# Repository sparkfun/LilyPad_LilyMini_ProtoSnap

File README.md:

LilyMini ProtoSnap
========================================

[*LilyMini ProtoSnap (https://www.sparkfun.com/products/14063)*](https://www.sparkfun.com/products/14063)

The LilyMini ProtoSnap is a great way to create interactive e-textile circuits. At the center of the board is a pre-programmed LilyMini microcontroller connected to a LilyPad Light Sensor, LilyPad Button and two pairs of LilyPad LEDs.

Like other ProtoSnap boards, the LilyMini ProtoSnap has all of these parts connected together on the board, enabling you to play with the circuit before you sew. When you're ready to make your project, snap out the parts and sew them together!

The LilyMini ProtoSnap ships with pre-loaded code that exercises all the LilyPad pieces connected to it. The sample code has three modes, which can be selected by pressing the LilyPad Button on the bottom-left side of the ProtoSnap. The built-in RGB LED on the LilyMini will change color to indicate which mode has been selected:

* White: All LEDs on.
* Magenta: LEDs fade in and out in a breathing pattern. When the light sensor is covered, LEDs fade faster.
* Cyan/Blue: When the board is in darkness, the LEDs will twinkle (perfect for night-lights)

You can use the built-in code to make your own projects (see the hook-up guide below), or you can reprogram the LilyMini using the Arduino system . **Reprogramming instructions coming soon (1/1/17).** 

Repository Contents
-------------------

This repository includes the hardware design files and binaries for the release firmware. <br>
**Reprogramming information and source code are coming soon (1/1/17).** 

* **/Documentation** - Data sheets, additional product information
* **/Firmware** - Preinstalled code 
* **/Hardware** - Eagle design files (.brd, .sch)
* **/Production** - Production panel files (.brd)

Documentation
--------------
* **[Hookup Guide](https://learn.sparkfun.com/tutorials/lilymini-protosnap-hookup-guide)** - Basic hookup guide and example projects for the LilyMini ProtoSnap

License Information
-------------------

This product is _**open source**_! Please review the LICENSE.md file for license information. If you have any questions or concerns on licensing, please contact techsupport@sparkfun.com. This information is distributed as-is; no warranty is given.

Have fun! - Your friends at SparkFun.

Acknowledgement
---------------

We gratefully acknowledge the following people and groups for their open-source contributions:

* Arduino LLC and Atmel Corporation/Thibaut Viard for bringing Arduino support to the SAMD21.
* Justin Mattair of [Mattairtech, Inc.](https://www.mattairtech.com/) for porting Arduino's SAMD21 bootloader and Shumatech's BOSSAC to the SAMD11.

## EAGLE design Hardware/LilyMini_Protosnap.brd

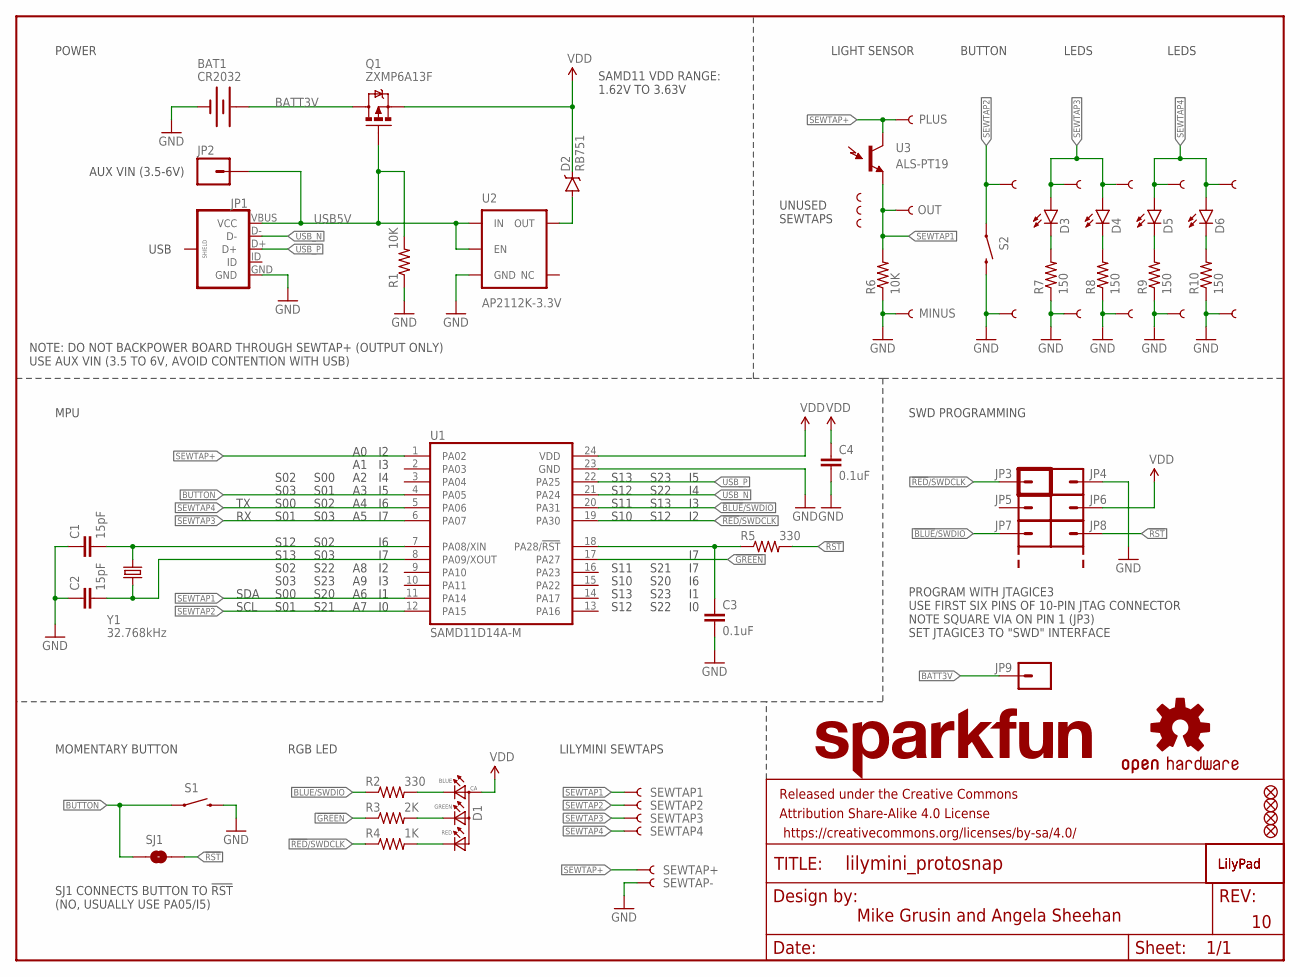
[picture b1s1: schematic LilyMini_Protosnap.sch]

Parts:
$1_61_$_2016-09-25_21-56-09: OSHW-LOGOS; OSHW-LOGO-S
BAT1: CR2032; BATTERY_20MM_PTH_KIT
C1, C2: 15pF; 0603-CAP
C3, C4: 0.1uF; 0603-CAP
D1: 0.13_RGB_LEDPLCC; P-LCC-4-3
D2: RB751; SOD-523
D3, D4, D5, D6: LED-WHITE1206; LED-1206
FD1, FD2, FD3, FD4: FIDUCIAL1X2; FIDUCIAL-1X2
FRAME1: FRAME-LETTER; CREATIVE_COMMONS
JP1: USB_MICROB_PLUGUSB-B-MICRO-SMD-VERT; USB-B-MICRO-SMD_VERT
JP2: M01SMDNS; 1X01NS
JP3: M01_POGOPAD_20M_NS_1S_SQUARE; 1X01_POGOPIN_PAD_NOSILK_1SIDE_SQUARE
JP4, JP5, JP6, JP7, JP8, JP9: M01_POGOPAD_20M_NS_1S_ROUND; 1X01_POGOPIN_PAD_NOSILK_1SIDE_ROUND
JP12, JP13: SEWTAP8; PETAL-MEDIUM-2SIDE
JP20, JP21, JP22, JP23, JP24, JP25, JP26, JP27: SEWTAP6; PETAL-SMALL-2SIDE
LOGO1: LOGO-LPL; LOGO-L
LOGO2: LILYLOGO-L-TOP; LOGO-L-TOP
LOGO4: SFE_LOGO_NAME.1_INCH; SFE_LOGO_NAME_.1
Q1: ZXMP6A13F; SOT23-3
R1, R6: 10K; 0603-RES
R2, R5: 330; 0603-RES
R3: 2K; 0603-RES
R4: 1K; 0603-RES
R7, R8, R9, R10: 150; 0603-RES
S1: SWITCH-MOMENTARY-2SMD-4.6X2.8MM; TACTILE_SWITCH_SMD_4.6X2.8MM
S2: SWITCH-MOMENTARY-2SMD-REDUNDANT; TACTILE-SWITCH-SMD
SEWTAP1, SEWTAP2, SEWTAP3, SEWTAP4: SEWTAP8; PETAL-MEDIUM-2SIDE
SEWTAP+: SEWTAP8; PETAL-MEDIUM-2SIDE
SEWTAP-: SEWTAP8; PETAL-MEDIUM-2SIDE
SEWTAPLS+: PLUS; PETAL-SMALL-2SIDE
SEWTAPLS-: MINUS; PETAL-SMALL-2SIDE
SEWTAPLSOUT: OUT; PETAL-SMALL-2SIDE
SJ1: JUMPER-PAD-2-NO; PAD-JUMPER-2-NO_NO_SILK
ST1, ST2, ST3: SEWTAP-NOHOLE2; PETAL-NOHOLE-2SIDE
U1: SAMD11D14A-M; QFN-24_ALT2
U2: AP2112K-3.3V; SOT23-5
U3: ALS-PT19
Y1: 32.768kHz; CRYSTAL-SMD-3.2X1.5MM

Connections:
!BLUE!/SWDIO: JP7.P$1, R2.1, U1.20 (PA31)
!GREEN!: R3.1, U1.17 (PA27)
!RED!/SWDCLK: JP3.P$1, R4.1, U1.19 (PA30)
!RST!: JP8.P$1, R5.2, SJ1.2
!RST!1: C3.1, R5.1, U1.18 (PA28/!RST!)
B: D1.3 (BLUE), R2.2
BATT3V: BAT1.+1 (+), BAT1.+2 (+), JP9.P$1, Q1.3 (D)
BUTTON: S1.1, S1.2 (1), SJ1.1, U1.4 (PA05)
G: D1.2 (GREEN), R3.2
GND: BAT1.-3 (-), C1.1, C2.1, C3.2, C4.2, JP1.GND, JP4.P$1, JP13.1, JP21.1, JP23.1, JP25.1, JP27.1, R1.1, R6.1, R7.1, R8.1, R9.1, R10.1, S1.3 (2), S1.4 (2), S2.3 (2), S2.4 (2), SEWTAP-.1, SEWTAPLS-.1, U1.23 (GND), U2.2 (GND)
unnamed: D2.A, U2.5 (OUT)
unnamed: D3.C, R7.2
unnamed: D4.C, R8.2
unnamed: D5.C, R9.2
unnamed: D6.C, R10.2
R: D1.1 (RED), R4.2
SEWTAP1: R6.2, SEWTAP1.1, SEWTAPLSOUT.1, U1.11 (PA14), U3.E (E1)
SEWTAP2: JP12.1, S2.1, S2.2 (1), SEWTAP2.1, U1.12 (PA15)
SEWTAP3: D3.A, D4.A, JP20.1, JP22.1, SEWTAP3.1, U1.6 (PA07)
SEWTAP4: D5.A, D6.A, JP24.1, JP26.1, SEWTAP4.1, U1.5 (PA06)
SEWTAP+: SEWTAP+.1, SEWTAPLS+.1, U1.1 (PA02), U3.C (C1)
USB5V: JP1.VBUS (VCC), JP2.1, Q1.1 (G), R1.2, U2.1 (IN), U2.3 (EN)
USB_N: JP1.D-, U1.21 (PA24)
USB_P: JP1.D+, U1.22 (PA25)
VDD: C4.1, D1.4 (ANODE), D2.C, JP6.P$1, Q1.2 (S), U1.24 (VDD)
X1: C1.2, U1.7 (PA08/XIN), Y1.P$2 (2)
X2: C2.2, U1.8 (PA09/XOUT), Y1.P$1 (1)

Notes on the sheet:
PROGRAM WITH JTAGICE3 USE FIRST SIX PINS OF 10-PIN JTAG CONNECTOR NOTE SQUARE VIA ON PIN 1 (JP3) SET JTAGICE3 TO "SWD" INTERFACE
SAMD11 VDD RANGE: 1.62V TO 3.63V
SWD PROGRAMMING
RGB LED
MOMENTARY BUTTON
S00
S01
S03
S02
SDA
SCL
AUX VIN (3.5-6V)
UNUSED SEWTAPS
Mike Grusin and Angela Sheehan
LILYMINI SEWTAPS
S22
S23
S20
S21
LIGHT SENSOR
BUTTON
LEDS
USB
NOTE: DO NOT BACKPOWER BOARD THROUGH SEWTAP+ (OUTPUT ONLY) USE AUX VIN (3.5 TO 6V, AVOID CONTENTION WITH USB)
S12
S13
S11
S10
POWER
MPU
SJ1 CONNECTS BUTTON TO !RST! (NO, USUALLY USE PA05/I5)

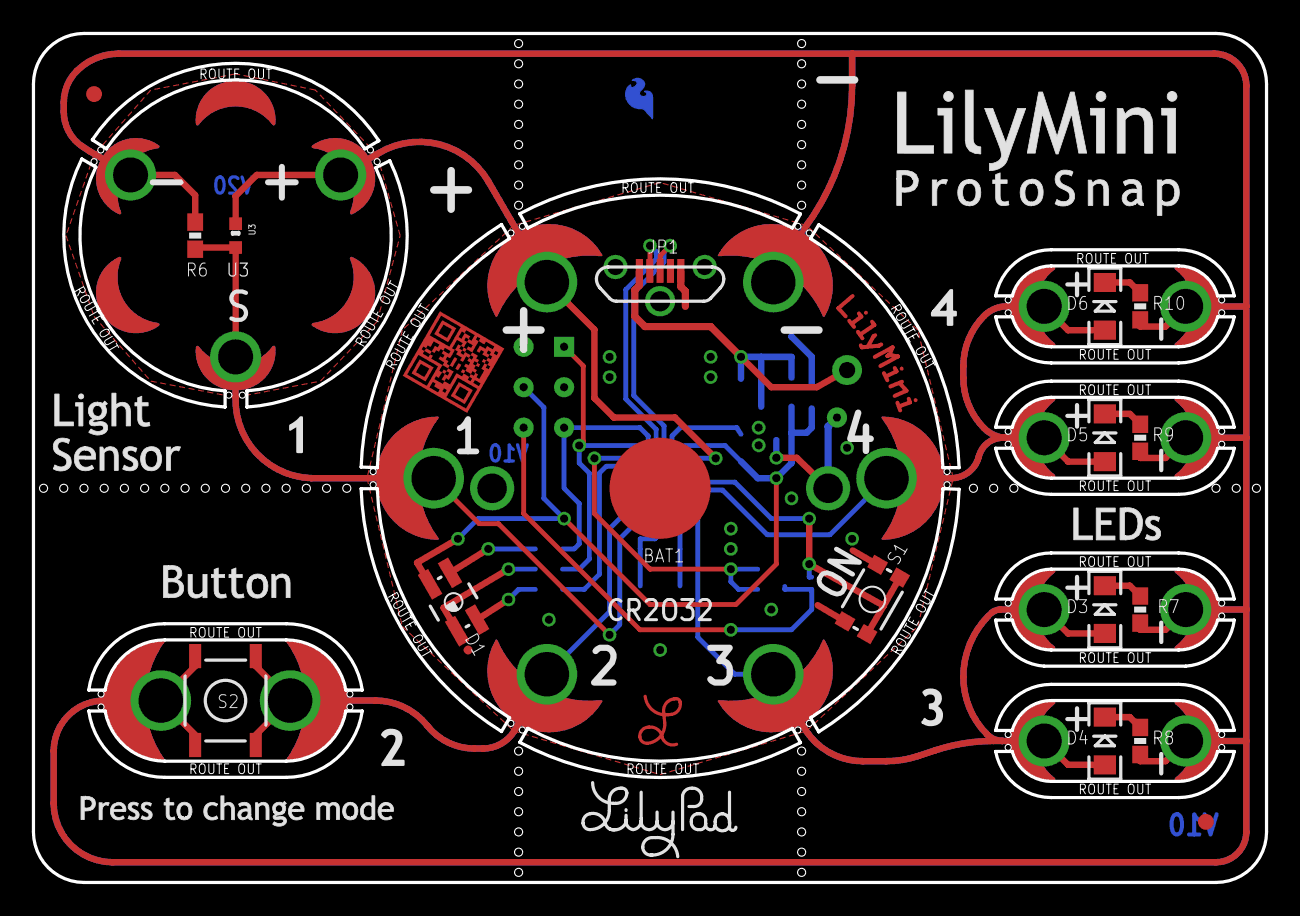
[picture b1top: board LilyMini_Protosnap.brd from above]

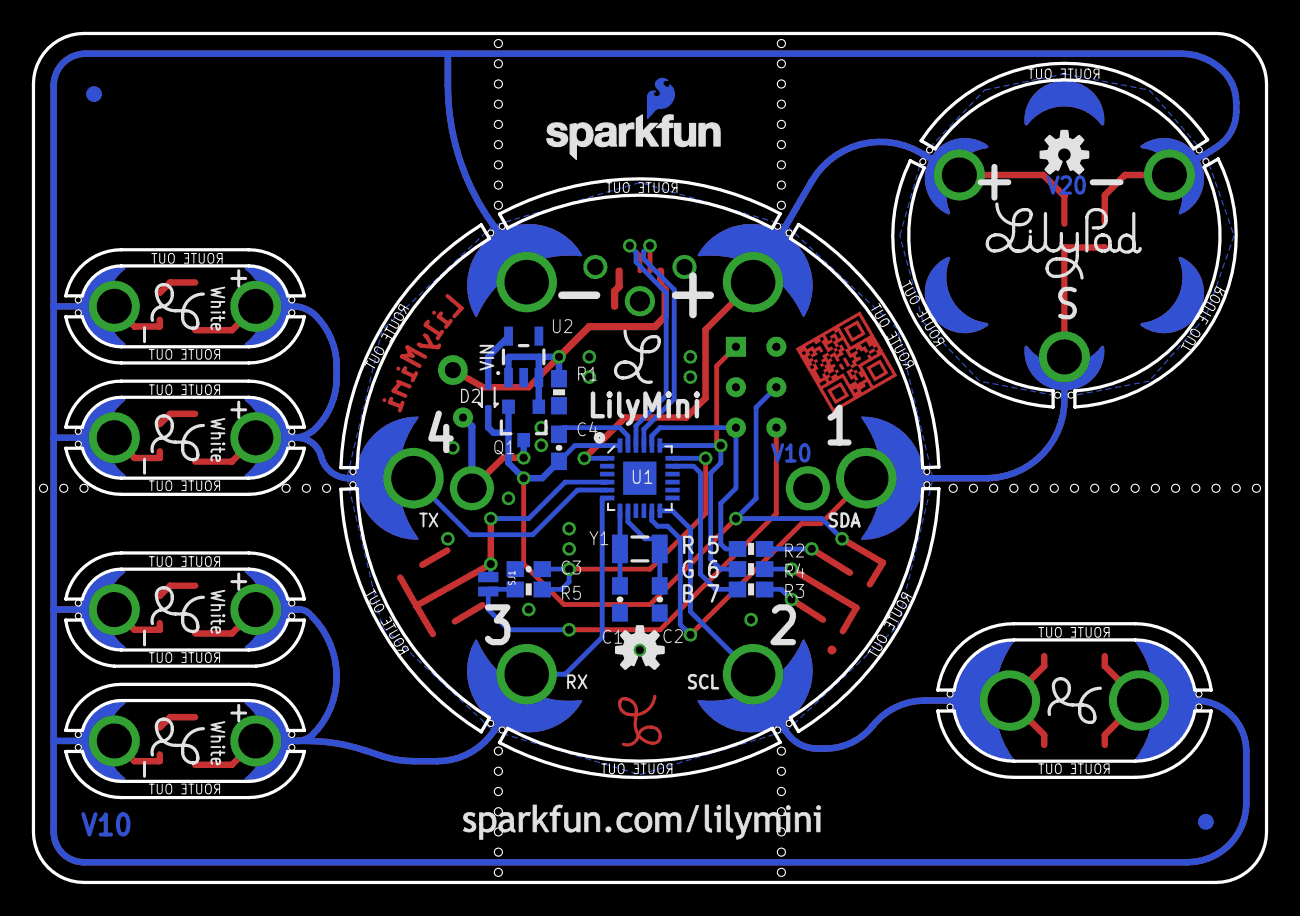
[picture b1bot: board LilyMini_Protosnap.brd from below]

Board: 2 copper layers, 77.5 x 53.3 mm, 78 parts (35 on the bottom side), 27 nets.

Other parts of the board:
LOGO3: OSHW-LOGOS; OSHW-LOGO-S
U$1: LOGO-LILYPAD
U$2: LOGO-LPLP; LOGO-LILYPAD
U$4: SFE_LOGO_FLAME_COPPER_EXPOSED_.1
U$5, U$6, U$7, U$8, U$9: LOGO-L

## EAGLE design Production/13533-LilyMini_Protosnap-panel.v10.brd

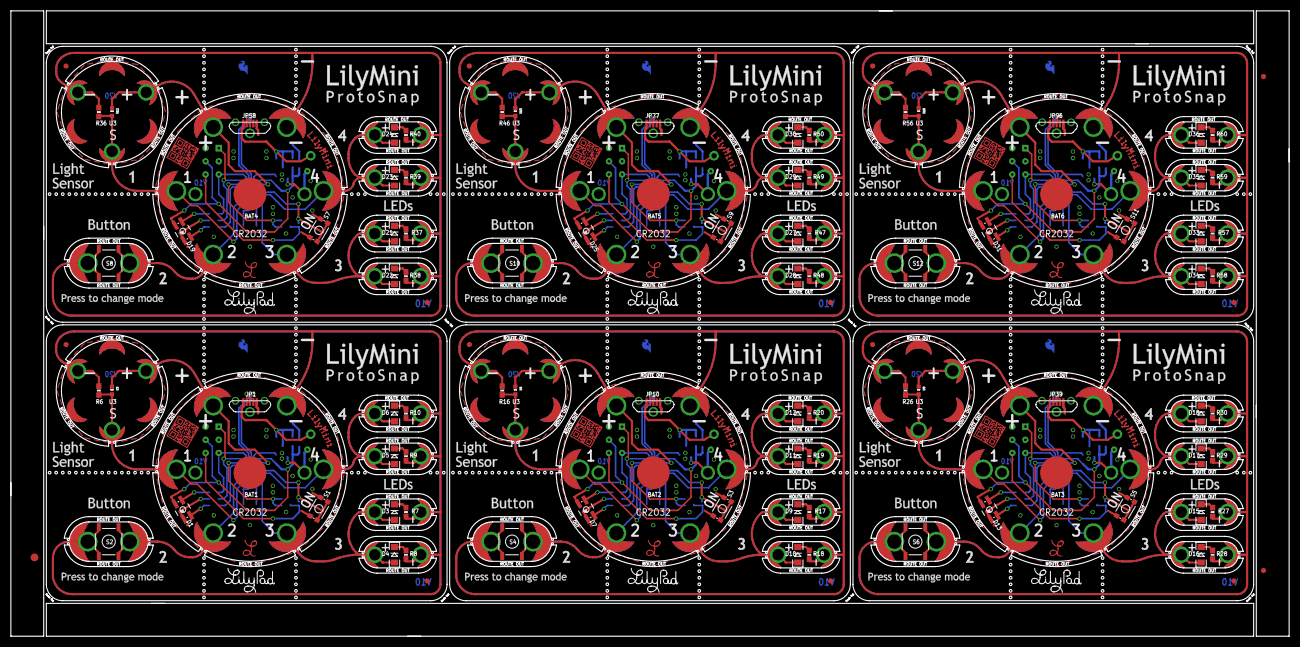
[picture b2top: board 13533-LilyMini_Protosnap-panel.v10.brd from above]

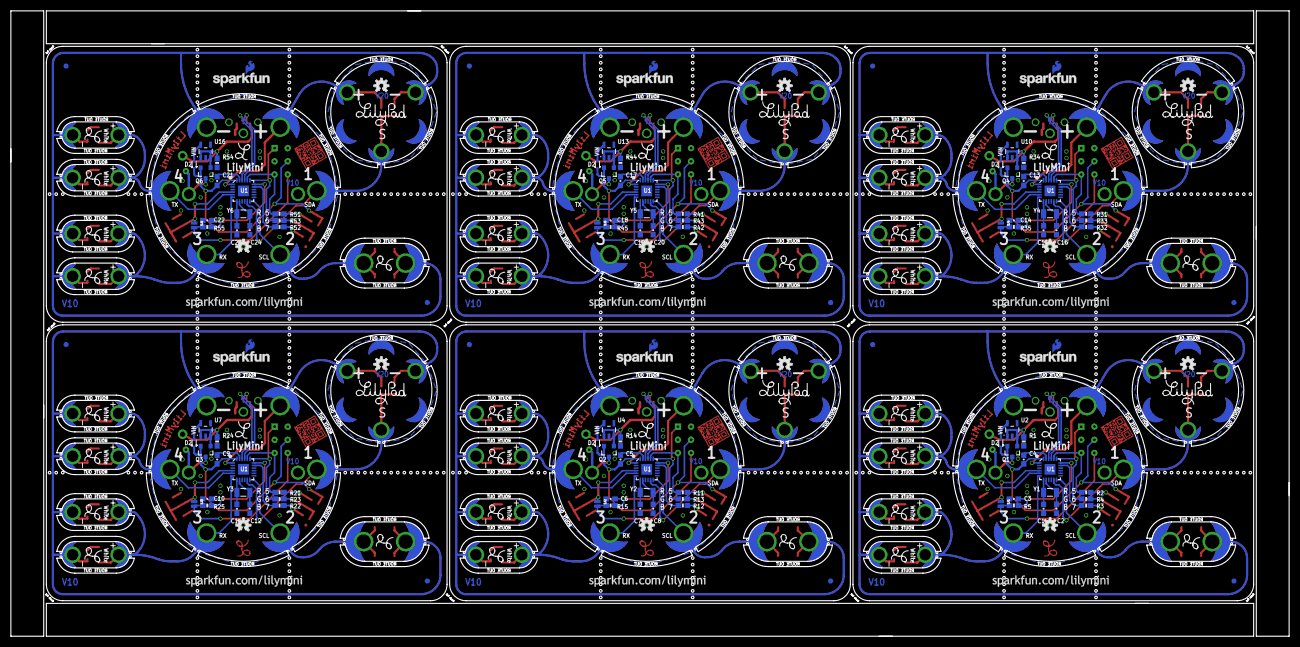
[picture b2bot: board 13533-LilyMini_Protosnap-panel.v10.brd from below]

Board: 2 copper layers, 247.1 x 120.9 mm, 465 parts (210 on the bottom side), 162 nets.

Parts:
$1_61_$_2016-09-25_21-56-01, $1_61_$_2016-09-25_21-56-02, $1_61_$_2016-09-25_21-56-03, $1_61_$_2016-09-25_21-56-04, $1_61_$_2016-09-25_21-56-05, $1_61_$_2016-09-25_21-56-09: OSHW-LOGOS; OSHW-LOGO-S
BAT1, BAT2, BAT3, BAT4, BAT5, BAT6: CR2032; BATTERY_20MM_PTH_KIT
C1, C2, C7, C8, C11, C12, C15, C16, C19, C20, C23, C24: 15pF; 0603-CAP
C3, C4, C5, C6, C9, C10, C13, C14, C17, C18, C21, C22: 0.1uF; 0603-CAP
D1, D7, D13, D19, D25, D31: P-LCC-4-3
D2, D8, D14, D20, D26, D32: RB751; SOD-523
D3, D4, D5, D6, D9, D10, D11, D12, D15, D16, D17, D18, D21, D22, D23, D24, D27, D28, D29, D30, D33, D34, D35, D36: LED-1206
E$1: FIDUCIAL-1.5X3
E$7, E$8: FIDUCIAL-1X2
FD1, FD2, FD3, FD4, FD5, FD6, FD7, FD8, FD9, FD10, FD11, FD12, FD13, FD14, FD15, FD16, FD17, FD18, FD19, FD20, FD21, FD22, FD23, FD24: FIDUCIAL1X2; FIDUCIAL-1X2
JP1, JP10, JP39, JP58, JP77, JP96: USB-B-MICRO-SMD_VERT
JP2, JP19, JP46, JP65, JP84, JP103: 1X01NS
JP3, JP11, JP40, JP59, JP78, JP97: 1X01_POGOPIN_PAD_NOSILK_1SIDE_SQUARE
JP4, JP5, JP6, JP7, JP8, JP9, JP14, JP15, JP16, JP17, JP18, JP38, JP41, JP42, JP43, JP44, JP45, JP57, JP60, JP61, JP62, JP63, JP64, JP76, JP79, JP80, JP81, JP82, JP83, JP95, JP98, JP99, JP100, JP101, JP102, JP114: 1X01_POGOPIN_PAD_NOSILK_1SIDE_ROUND
JP12, JP13, JP32, JP33, JP51, JP52, JP70, JP71, JP89, JP90, JP108, JP109: PETAL-MEDIUM-2SIDE
JP20, JP21, JP22, JP23, JP24, JP25, JP26, JP27, JP28, JP29, JP30, JP31, JP34, JP35, JP36, JP37, JP47, JP48, JP49, JP50, JP53, JP54, JP55, JP56, JP66, JP67, JP68, JP69, JP72, JP73, JP74, JP75, JP85, JP86, JP87, JP88, JP91, JP92, JP93, JP94, JP104, JP105, JP106, JP107, JP110, JP111, JP112, JP113: PETAL-SMALL-2SIDE
LOGO1, LOGO5, LOGO9, LOGO13, LOGO17, LOGO21: LOGO-L
LOGO2, LOGO6, LOGO10, LOGO14, LOGO18, LOGO22: LOGO-L-TOP
LOGO3, LOGO7, LOGO11, LOGO15, LOGO19, LOGO23: OSHW-LOGOS; OSHW-LOGO-S
LOGO4, LOGO8, LOGO12, LOGO16, LOGO20, LOGO24: SFE_LOGO_NAME.1_INCH; SFE_LOGO_NAME_.1
Q1, Q2, Q3, Q4, Q5, Q6: ZXMP6A13F; SOT23-3
R1, R6, R14, R16, R24, R26, R34, R36, R44, R46, R54, R56: 10K; 0603-RES
R2, R5, R11, R15, R21, R25, R31, R35, R41, R45, R51, R55: 330; 0603-RES
R3, R12, R22, R32, R42, R52: 2K; 0603-RES
R4, R13, R23, R33, R43, R53: 1K; 0603-RES
R7, R8, R9, R10, R17, R18, R19, R20, R27, R28, R29, R30, R37, R38, R39, R40, R47, R48, R49, R50, R57, R58, R59, R60: 150; 0603-RES
S1, S3, S5, S7, S9, S11: TACTILE_SWITCH_SMD_4.6X2.8MM
S2, S4, S6, S8, S10, S12: TACTILE-SWITCH-SMD
SEWTAP1, SEWTAP2, SEWTAP3, SEWTAP4, SEWTAP5, SEWTAP6, SEWTAP7, SEWTAP8, SEWTAP9, SEWTAP10, SEWTAP11, SEWTAP12, SEWTAP13, SEWTAP14, SEWTAP15, SEWTAP16, SEWTAP17, SEWTAP18, SEWTAP19, SEWTAP20, SEWTAP21, SEWTAP22, SEWTAP23, SEWTAP24: PETAL-MEDIUM-2SIDE
SEWTAP+, SEWTAP+1, SEWTAP+2, SEWTAP+3, SEWTAP+4, SEWTAP+5: PETAL-MEDIUM-2SIDE
SEWTAP-, SEWTAP-1, SEWTAP-2, SEWTAP-3, SEWTAP-4, SEWTAP-5: PETAL-MEDIUM-2SIDE
SEWTAPLS+, SEWTAPLS+1, SEWTAPLS+2, SEWTAPLS+3, SEWTAPLS+4, SEWTAPLS+5: PLUS; PETAL-SMALL-2SIDE
SEWTAPLS-, SEWTAPLS-1, SEWTAPLS-2, SEWTAPLS-3, SEWTAPLS-4, SEWTAPLS-5: MINUS; PETAL-SMALL-2SIDE
SEWTAPLSOUT, SEWTAPLSOUT1, SEWTAPLSOUT2, SEWTAPLSOUT3, SEWTAPLSOUT4, SEWTAPLSOUT5: OUT; PETAL-SMALL-2SIDE
SJ1, SJ2, SJ3, SJ4, SJ5, SJ6: PAD-JUMPER-2-NO_NO_SILK
ST1, ST2, ST3, ST4, ST5, ST6, ST7, ST8, ST9, ST10, ST11, ST12, ST13, ST14, ST15, ST16, ST17, ST18: PETAL-NOHOLE-2SIDE
U1, U5, U8, U11, U14, U17: SAMD11D14A-M; QFN-24_ALT2
U2, U4, U7, U10, U13, U16: AP2112K-3.3V; SOT23-5
U3, U6, U9, U12, U15, U18: ALS-PT19
U$1, U$13, U$21, U$29, U$37, U$45: LOGO-LILYPAD
U$2, U$3, U$17, U$25, U$33, U$41: LOGO-LPLP; LOGO-LILYPAD
U$4, U$10, U$18, U$26, U$34, U$42: SFE_LOGO_FLAME_COPPER_EXPOSED_.1
U$5, U$6, U$7, U$8, U$9, U$11, U$12, U$14, U$15, U$16, U$19, U$20, U$22, U$23, U$24, U$27, U$28, U$30, U$31, U$32, U$35, U$36, U$38, U$39, U$40, U$43, U$44, U$46, U$47, U$48: LOGO-L
Y1, Y2, Y3, Y4, Y5, Y6: 32.768kHz; CRYSTAL-SMD-3.2X1.5MM

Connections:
!BLUE!/SWDIO: JP7.P$1, R2.1, U1.20
!BLUE!/SWDIO1: JP17.P$1, R11.1, U5.20
!BLUE!/SWDIO2: JP44.P$1, R21.1, U8.20
!BLUE!/SWDIO3: JP63.P$1, R31.1, U11.20
!BLUE!/SWDIO4: JP82.P$1, R41.1, U14.20
!BLUE!/SWDIO5: JP101.P$1, R51.1, U17.20
!GREEN!: R3.1, U1.17
!GREEN!1: R12.1, U5.17
!GREEN!2: R22.1, U8.17
!GREEN!3: R32.1, U11.17
!GREEN!4: R42.1, U14.17
!GREEN!5: R52.1, U17.17
!RED!/SWDCLK: JP3.P$1, R4.1, U1.19
!RED!/SWDCLK1: JP11.P$1, R13.1, U5.19
!RED!/SWDCLK2: JP40.P$1, R23.1, U8.19
!RED!/SWDCLK3: JP59.P$1, R33.1, U11.19
!RED!/SWDCLK4: JP78.P$1, R43.1, U14.19
!RED!/SWDCLK5: JP97.P$1, R53.1, U17.19
!RST!: JP8.P$1, R5.2, SJ1.2
!RST!1: C3.1, R5.1, U1.18
!RST!2: JP18.P$1, R15.2, SJ2.2
!RST!3: C6.1, R15.1, U5.18
!RST!4: JP45.P$1, R25.2, SJ3.2
!RST!5: C10.1, R25.1, U8.18
!RST!6: JP64.P$1, R35.2, SJ4.2
!RST!7: C14.1, R35.1, U11.18
!RST!8: JP83.P$1, R45.2, SJ5.2
!RST!9: C18.1, R45.1, U14.18
!RST!10: JP102.P$1, R55.2, SJ6.2
!RST!11: C22.1, R55.1, U17.18
B: D1.3, R2.2
B1: D7.3, R11.2
B2: D13.3, R21.2
B3: D19.3, R31.2
B4: D25.3, R41.2
B5: D31.3, R51.2
BATT3V: BAT1.+1, BAT1.+2, JP9.P$1, Q1.3
BATT3V1: BAT2.+1, BAT2.+2, JP38.P$1, Q2.3
BATT3V2: BAT3.+1, BAT3.+2, JP57.P$1, Q3.3
BATT3V3: BAT4.+1, BAT4.+2, JP76.P$1, Q4.3
BATT3V4: BAT5.+1, BAT5.+2, JP95.P$1, Q5.3
BATT3V5: BAT6.+1, BAT6.+2, JP114.P$1, Q6.3
BUTTON: S1.1, S1.2, SJ1.1, U1.4
BUTTON1: S3.1, S3.2, SJ2.1, U5.4
BUTTON2: S5.1, S5.2, SJ3.1, U8.4
BUTTON3: S7.1, S7.2, SJ4.1, U11.4
BUTTON4: S9.1, S9.2, SJ5.1, U14.4
BUTTON5: S11.1, S11.2, SJ6.1, U17.4
G: D1.2, R3.2
G1: D7.2, R12.2
G2: D13.2, R22.2
G3: D19.2, R32.2
G4: D25.2, R42.2
G5: D31.2, R52.2
GND: BAT1.-3, C1.1, C2.1, C3.2, C4.2, JP1.GND, JP4.P$1, JP13.1, JP21.1, JP23.1, JP25.1, JP27.1, R1.1, R6.1, R7.1, R8.1, R9.1, R10.1, S1.3, S1.4, S2.3, S2.4, SEWTAP-.1, SEWTAPLS-.1, U1.23, U2.2
GND1: BAT2.-3, C5.2, C6.2, C7.1, C8.1, JP10.GND, JP14.P$1, JP28.1, JP29.1, JP30.1, JP31.1, JP32.1, R14.1, R16.1, R17.1, R18.1, R19.1, R20.1, S3.3, S3.4, S4.3, S4.4, SEWTAP-1.1, SEWTAPLS-1.1, U4.2, U5.23
GND3: BAT3.-3, C9.2, C10.2, C11.1, C12.1, JP39.GND, JP41.P$1, JP47.1, JP48.1, JP49.1, JP50.1, JP51.1, R24.1, R26.1, R27.1, R28.1, R29.1, R30.1, S5.3, S5.4, S6.3, S6.4, SEWTAP-2.1, SEWTAPLS-2.1, U7.2, U8.23
GND6: BAT4.-3, C13.2, C14.2, C15.1, C16.1, JP58.GND, JP60.P$1, JP66.1, JP67.1, JP68.1, JP69.1, JP70.1, R34.1, R36.1, R37.1, R38.1, R39.1, R40.1, S7.3, S7.4, S8.3, S8.4, SEWTAP-3.1, SEWTAPLS-3.1, U10.2, U11.23
GND8: BAT5.-3, C17.2, C18.2, C19.1, C20.1, JP77.GND, JP79.P$1, JP85.1, JP86.1, JP87.1, JP88.1, JP89.1, R44.1, R46.1, R47.1, R48.1, R49.1, R50.1, S9.3, S9.4, S10.3, S10.4, SEWTAP-4.1, SEWTAPLS-4.1, U13.2, U14.23
GND10: BAT6.-3, C21.2, C22.2, C23.1, C24.1, JP96.GND, JP98.P$1, JP104.1, JP105.1, JP106.1, JP107.1, JP108.1, R54.1, R56.1, R57.1, R58.1, R59.1, R60.1, S11.3, S11.4, S12.3, S12.4, SEWTAP-5.1, SEWTAPLS-5.1, U16.2, U17.23
unnamed: D2.A, U2.5
unnamed: D3.C, R7.2
unnamed: D4.C, R8.2
unnamed: D5.C, R9.2
unnamed: D6.C, R10.2
unnamed: D8.A, U4.5
unnamed: D9.C, R17.2
unnamed: D10.C, R18.2
unnamed: D11.C, R19.2
unnamed: D12.C, R20.2
unnamed: D14.A, U7.5
unnamed: D15.C, R27.2
unnamed: D16.C, R28.2
unnamed: D17.C, R29.2
unnamed: D18.C, R30.2
unnamed: D20.A, U10.5
unnamed: D21.C, R37.2
unnamed: D22.C, R38.2
unnamed: D23.C, R39.2
unnamed: D24.C, R40.2
unnamed: D26.A, U13.5
unnamed: D27.C, R47.2
unnamed: D28.C, R48.2
unnamed: D29.C, R49.2
unnamed: D30.C, R50.2
unnamed: D32.A, U16.5
unnamed: D33.C, R57.2
unnamed: D34.C, R58.2
unnamed: D35.C, R59.2
unnamed: D36.C, R60.2
R: D1.1, R4.2
R1: D7.1, R13.2
R2: D13.1, R23.2
R3: D19.1, R33.2
R4: D25.1, R43.2
R5: D31.1, R53.2
SEWTAP1: R6.2, SEWTAP1.1, SEWTAPLSOUT.1, U1.11, U3.E
SEWTAP2: JP12.1, S2.1, S2.2, SEWTAP2.1, U1.12
SEWTAP3: D3.A, D4.A, JP20.1, JP22.1, SEWTAP3.1, U1.6
SEWTAP4: D5.A, D6.A, JP24.1, JP26.1, SEWTAP4.1, U1.5
SEWTAP9: R16.2, SEWTAP5.1, SEWTAPLSOUT1.1, U5.11, U6.E
SEWTAP10: JP33.1, S4.1, S4.2, SEWTAP6.1, U5.12
SEWTAP11: D11.A, D12.A, JP36.1, JP37.1, SEWTAP8.1, U5.5
SEWTAP12: D9.A, D10.A, JP34.1, JP35.1, SEWTAP7.1, U5.6
SEWTAP17: R26.2, SEWTAP9.1, SEWTAPLSOUT2.1, U8.11, U9.E
SEWTAP18: JP52.1, S6.1, S6.2, SEWTAP10.1, U8.12
SEWTAP19: D17.A, D18.A, JP55.1, JP56.1, SEWTAP12.1, U8.5
SEWTAP20: D15.A, D16.A, JP53.1, JP54.1, SEWTAP11.1, U8.6
SEWTAP25: R36.2, SEWTAP13.1, SEWTAPLSOUT3.1, U11.11, U12.E
SEWTAP26: JP71.1, S8.1, S8.2, SEWTAP14.1, U11.12
SEWTAP27: D23.A, D24.A, JP74.1, JP75.1, SEWTAP16.1, U11.5
SEWTAP28: D21.A, D22.A, JP72.1, JP73.1, SEWTAP15.1, U11.6
SEWTAP33: R46.2, SEWTAP17.1, SEWTAPLSOUT4.1, U14.11, U15.E
SEWTAP34: JP90.1, S10.1, S10.2, SEWTAP18.1, U14.12
SEWTAP35: D29.A, D30.A, JP93.1, JP94.1, SEWTAP20.1, U14.5
SEWTAP36: D27.A, D28.A, JP91.1, JP92.1, SEWTAP19.1, U14.6
SEWTAP41: R56.2, SEWTAP21.1, SEWTAPLSOUT5.1, U17.11, U18.E
SEWTAP42: JP109.1, S12.1, S12.2, SEWTAP22.1, U17.12
SEWTAP43: D35.A, D36.A, JP112.1, JP113.1, SEWTAP24.1, U17.5
SEWTAP44: D33.A, D34.A, JP110.1, JP111.1, SEWTAP23.1, U17.6
SEWTAP+: SEWTAP+.1, SEWTAPLS+.1, U1.1, U3.C
SEWTAP+2: SEWTAP+1.1, SEWTAPLS+1.1, U5.1, U6.C
SEWTAP+4: SEWTAP+2.1, SEWTAPLS+2.1, U8.1, U9.C
SEWTAP+6: SEWTAP+3.1, SEWTAPLS+3.1, U11.1, U12.C
SEWTAP+8: SEWTAP+4.1, SEWTAPLS+4.1, U14.1, U15.C
SEWTAP+10: SEWTAP+5.1, SEWTAPLS+5.1, U17.1, U18.C
USB5V: JP1.VBUS, JP2.1, Q1.1, R1.2, U2.1, U2.3
USB5V1: JP10.VBUS, JP19.1, Q2.1, R14.2, U4.1, U4.3
USB5V2: JP39.VBUS, JP46.1, Q3.1, R24.2, U7.1, U7.3
USB5V3: JP58.VBUS, JP65.1, Q4.1, R34.2, U10.1, U10.3
USB5V4: JP77.VBUS, JP84.1, Q5.1, R44.2, U13.1, U13.3
USB5V5: JP96.VBUS, JP103.1, Q6.1, R54.2, U16.1, U16.3
USB_N: JP1.D-, U1.21
USB_N1: JP10.D-, U5.21
USB_N2: JP39.D-, U8.21
USB_N3: JP58.D-, U11.21
USB_N4: JP77.D-, U14.21
USB_N5: JP96.D-, U17.21
USB_P: JP1.D+, U1.22
USB_P1: JP10.D+, U5.22
USB_P2: JP39.D+, U8.22
USB_P3: JP58.D+, U11.22
USB_P4: JP77.D+, U14.22
USB_P5: JP96.D+, U17.22
VDD: C4.1, D1.4, D2.C, JP6.P$1, Q1.2, U1.24
VDD1: C5.1, D7.4, D8.C, JP16.P$1, Q2.2, U5.24
VDD2: C9.1, D13.4, D14.C, JP43.P$1, Q3.2, U8.24
VDD3: C13.1, D19.4, D20.C, JP62.P$1, Q4.2, U11.24
VDD4: C17.1, D25.4, D26.C, JP81.P$1, Q5.2, U14.24
VDD5: C21.1, D31.4, D32.C, JP100.P$1, Q6.2, U17.24
X1: C1.2, U1.7, Y1.P$2
X2: C2.2, U1.8, Y1.P$1
X3: C8.2, U5.8, Y2.P$1
X4: C7.2, U5.7, Y2.P$2
X5: C12.2, U8.8, Y3.P$1
X6: C11.2, U8.7, Y3.P$2
X7: C16.2, U11.8, Y4.P$1
X8: C15.2, U11.7, Y4.P$2
X9: C20.2, U14.8, Y5.P$1
X10: C19.2, U14.7, Y5.P$2
X11: C24.2, U17.8, Y6.P$1
X12: C23.2, U17.7, Y6.P$2

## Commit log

2016-09-28 Added RGB "pin" designators to bplace
2016-09-28 Minor tweaks per board review checklist
2016-09-28 Minor changes based on AC and Bob's advice
    Reduced paste on QFN and USB footprints by 25%
2016-09-28 Found, fixed issue w QFN24 package :P
    Our libraries are the best.
2016-09-29 Changed mouse bites from 0.02 to 0.015
    Per Advanced Circuits, annular around original 0.02 drill hits would
    reduce trace to hairline. Drills reduced to 0.015 to reduce this issue.
    Smaller drills may make snapping harder, evaluate on proto.
2016-10-10 Minor changes pre review
    Enlarged copper on programming pins
    Added VBATT3 test point
    Added TDOCU text for test points
2016-10-10 Minor updates
    Larger fiducials
    Sep version numbers on snap (1), LilyMini (1), light (2 - layout and
    part change from current)
    Added perforations
2016-10-12 Changes per red review
    LED resistors to 150 ohm
    VBAT3V test point moved for selective solder
    USB P/N lines moved to rear of board for clearance and impedance control
    Perforations
2016-10-13 Minor changes per checklist
2016-10-18 panel
2016-11-11 Fixed typo on schematic
2016-12-10 Added production firmware V10
2016-12-15 Copied schematic to hardware folder
2016-12-15 Readme updates
2016-12-15 Minor readme edits

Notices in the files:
parts and their libraries:
SparkFun-Aesthetics: Licensing: Creative Commons ShareAlike 4.0 International - https://creativecommons.org/licenses/by-sa/4.0
SparkFun-Aesthetics: Released under the Creative Commons Attribution Share-Alike 4.0 License
SparkFun-Aesthetics: https://creativecommons.org/licenses/by-sa/4.0
